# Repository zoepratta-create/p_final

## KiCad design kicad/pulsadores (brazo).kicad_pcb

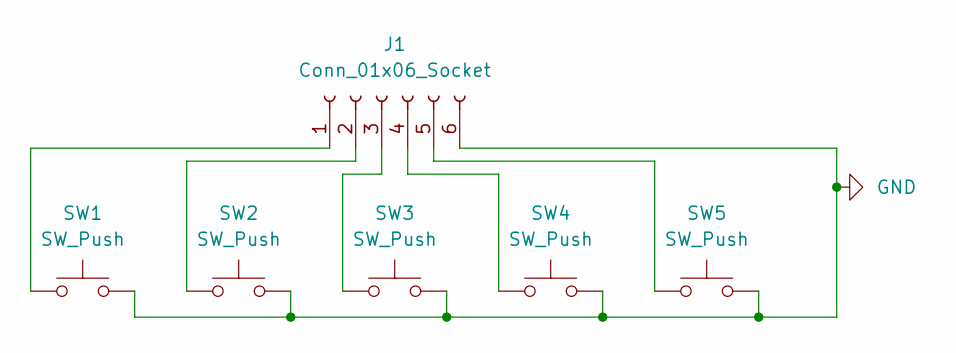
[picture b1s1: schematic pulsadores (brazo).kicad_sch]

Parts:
J1: Conn_01x06_Socket; PinSocket_1x06_P2.54mm_Vertical
SW1, SW2, SW3, SW4, SW5: SW_Push; SW_PUSH_6mm

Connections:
GND: J1.6, SW1.2, SW2.2, SW3.2, SW4.2, SW5.2
unnamed: J1.1, SW1.1
unnamed: J1.2, SW2.1
unnamed: J1.3, SW3.1
unnamed: J1.4, SW4.1
unnamed: J1.5, SW5.1

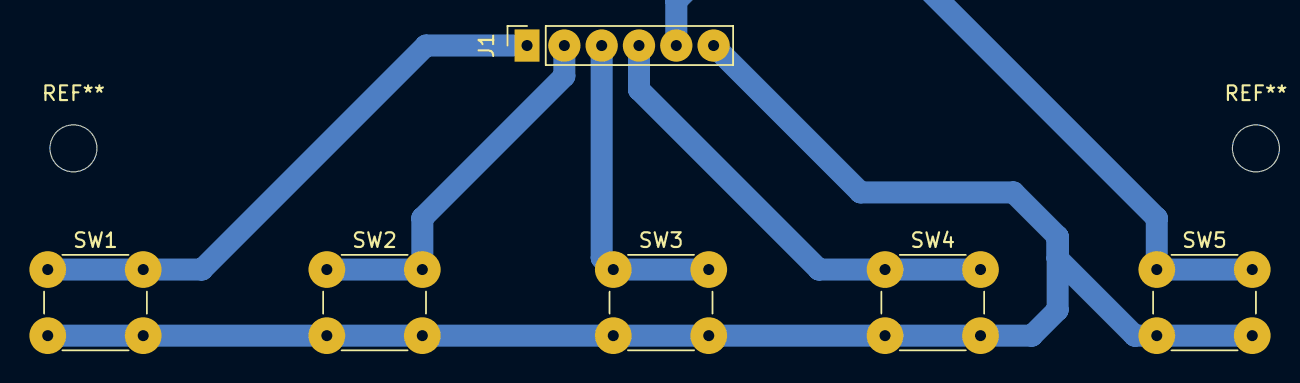
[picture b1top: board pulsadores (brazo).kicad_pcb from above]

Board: 2 copper layers, 6 parts (0 on the bottom side), 6 nets.

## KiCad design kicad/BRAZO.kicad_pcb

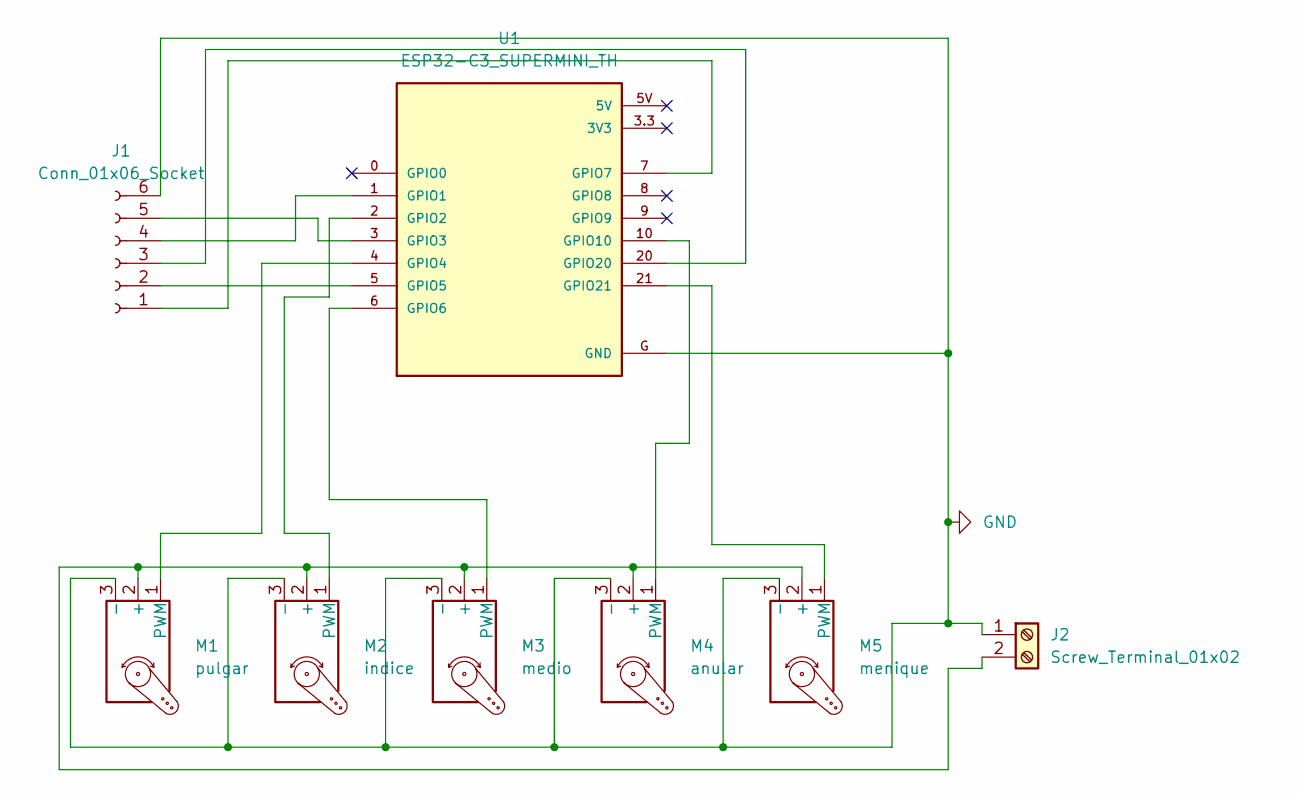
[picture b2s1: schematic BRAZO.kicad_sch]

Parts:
J1: Conn_01x06_Socket; PinSocket_1x06_P2.54mm_Vertical
J2: Screw_Terminal_01x02; TerminalBlock_MaiXu_MX126-5.0-02P_1x02_P5.00mm
M1: pulgar; PinSocket_1x03_P2.54mm_Vertical
M2: indice; PinSocket_1x03_P2.54mm_Vertical
M3: medio; PinSocket_1x03_P2.54mm_Vertical
M4: anular; PinSocket_1x03_P2.54mm_Vertical
M5: menique; PinSocket_1x03_P2.54mm_Vertical
U1: ESP32-C3_SUPERMINI_TH; MODULE_ESP32-C3_SUPERMINI_TH

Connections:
GND: J1.6, J2.1, M1.3 (-), M2.3 (-), M3.3 (-), M4.3 (-), M5.3 (-), U1.G (GND)
unnamed: J1.1, U1.7 (GPIO7)
unnamed: J1.2, U1.5 (GPIO5)
unnamed: J1.3, U1.20 (GPIO20)
unnamed: J1.4, U1.1 (GPIO1)
unnamed: J1.5, U1.3 (GPIO3)
unnamed: J2.2, M1.2 (+), M2.2 (+), M3.2 (+), M4.2 (+), M5.2 (+)
unnamed: M1.1 (PWM), U1.4 (GPIO4)
unnamed: M2.1 (PWM), U1.2 (GPIO2)
unnamed: M3.1 (PWM), U1.6 (GPIO6)
unnamed: M4.1 (PWM), U1.10 (GPIO10)
unnamed: M5.1 (PWM), U1.21 (GPIO21)

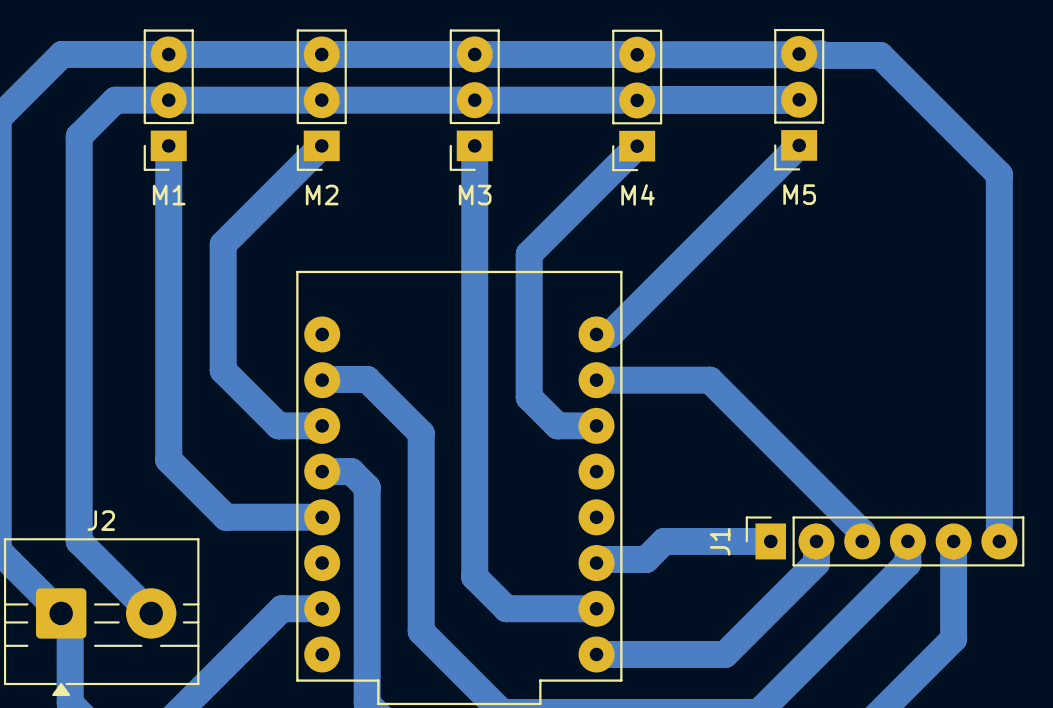
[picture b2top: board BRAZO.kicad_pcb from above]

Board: 2 copper layers, 8 parts (0 on the bottom side), 12 nets.
